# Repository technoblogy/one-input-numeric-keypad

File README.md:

# One-Input Numeric Keypad
A 12-key numeric keypad for use in microcontroller projects that only needs one analogue input to interface it.

See <http://www.technoblogy.com/show?41BI>.

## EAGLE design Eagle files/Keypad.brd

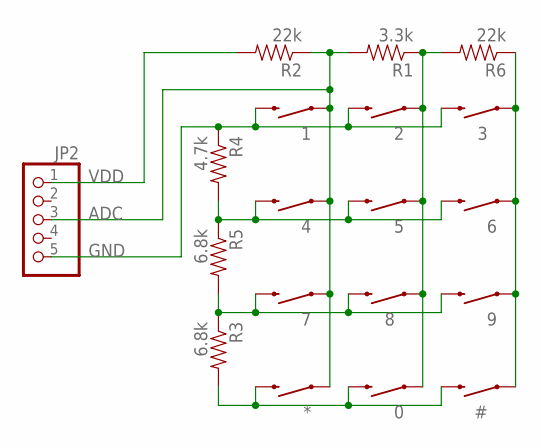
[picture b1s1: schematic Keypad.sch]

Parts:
0, 1, 2, 3, 4, 5, 6, 7, 8, 9: SWITCH-MOMENTARY-2PTH; TACTILE-PTH
#: SWITCH-MOMENTARY-2PTH; TACTILE-PTH
*: SWITCH-MOMENTARY-2PTH; TACTILE-PTH
JP2: HEADER-1X5ROUND; 1X05_ROUND
R1: 3.3k; 0805
R2, R6: 22k; 0805
R3, R5: 6.8k; 0805
R4: 4.7k; 0805

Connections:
ADC: 1.1, 4.1, 7.1, *.1, JP2.3, R1.2, R2.1
GND: 1.3 (2), 2.3 (2), 3.3 (2), JP2.5, R4.1
unnamed: 0.3 (2), #.3 (2), *.3 (2), R3.2
unnamed: 4.3 (2), 5.3 (2), 6.3 (2), R4.2, R5.1
unnamed: 7.3 (2), 8.3 (2), 9.3 (2), R3.1, R5.2
unnamed: 0.1, 2.1, 5.1, 8.1, R1.1, R6.2
unnamed: 3.1, 6.1, 9.1, #.1, R6.1
VDD: JP2.1, R2.2

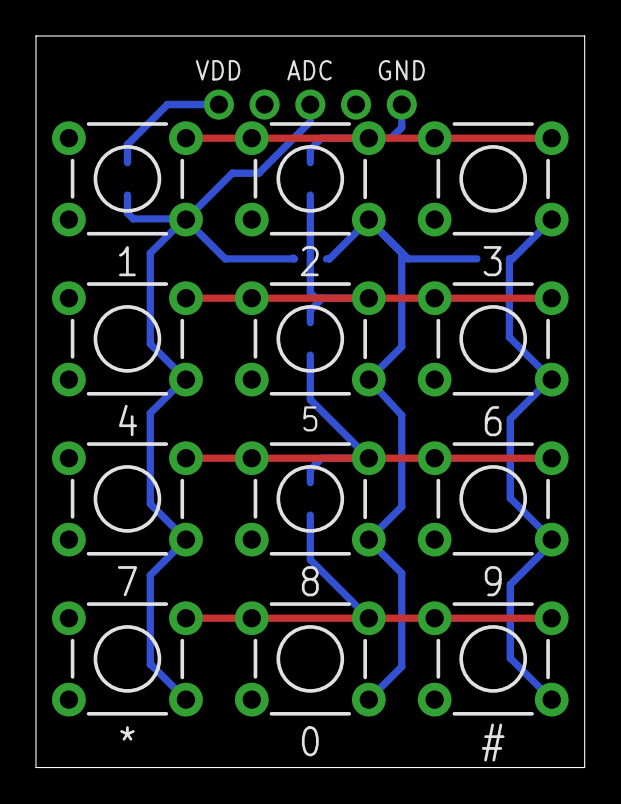
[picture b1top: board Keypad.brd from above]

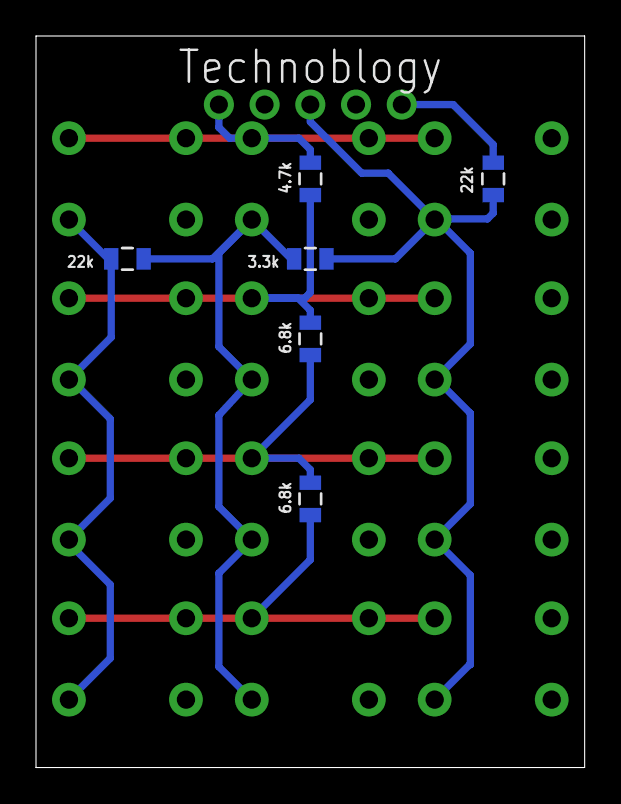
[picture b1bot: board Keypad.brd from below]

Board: 2 copper layers, 30.5 x 40.6 mm, 19 parts (6 on the bottom side), 8 nets.

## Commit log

2026-06-29 Version 1 - 29th June 2026

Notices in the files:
parts and their libraries:
SparkFun-Electromechanical: Licensing: Creative Commons ShareAlike 4.0 International - https://creativecommons.org/licenses/by-sa/4.0
SparkFun-Resistors: Licensing: CC v3.0 Share-Alike You are welcome to use this library for commercial purposes.
